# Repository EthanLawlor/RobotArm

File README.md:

# 🤖 Desktop Robot Arm

A compact, fully customizable desktop robot arm designed for small-scale automation tasks. Developed as part of a Bachelor of Engineering in Mechatronics at Technological University Dublin, this project integrates 3D-printed components, servo motor actuation, custom electronics, Arduino-based firmware, Bluetooth control, and an Android app interface.

*Figure: CAD render of the assembled Desktop Robot Arm*

---

## 📦 Features

- 6 Degrees of Freedom using MG66R and SG90 servo motors  
- Bluetooth-enabled control with HC-05 and MIT App Inventor  
- Android app with presets and direct manual controls  
- Custom PCB with schematics and Gerber files (KiCAD)  
- Modular 3D-printed design with STL files included  
- Smooth servo motion using filtering algorithms  

---

## 📁 Repository Structure

1. **Documentation**  
   - `RobotArm-ProjectReport.pdf` – Full project report with design, testing, and results

2. **Electrical**  
   - `KiCAD-PCB/` – Circuit schematics, custom PCB layout, and Gerber files

3. **Mechanical**  
   - `STL-Files/` – 3D-printable mechanical components  
   - Includes exploded views and CAD drawings

4. **Software**  
   - `Arduino-Firmware/` – Code for ATmega328P (Arduino)  
   - `MIT-App-Inventor/` – Android app `.aia` source and `.apk` installer

---

## 🔧 Hardware Overview

- **Microcontroller:** ATmega328P (Arduino Uno or custom board)  
- **Servos:** 5× MG66R, 1× SG90  
- **Peak Current Draw:** 2.8A (measured)  
- **Bluetooth Module:** HC-05  
- **Build Volume:** 135mm x 90mm footprint  
- **Chassis:** Fully 3D-printed components (PLA)  

---

## 📱 Android App

- Built with **MIT App Inventor**  
- Control individual servo angles or trigger gesture presets:
  - `Home`, `Ready`, `Wave`, `Screwdriver`, `Circles`, `Diagonals`, `Worm`, `Demo`
- Bluetooth communication with Arduino via HC-05  

---

## 📐 Mechanical Design

- All STL files for 3D printing included  
- Exploded views, BOM, and design drawings available  
- Desktop-sized and modular for easy assembly and customization  

---

## 🔌 Electrical Design

- Custom PCB designed in **KiCAD**  
- Includes:
  - Circuit schematics  
  - PCB layout  
  - Gerber files for fabrication  
- Power and signal headers for servos, Bluetooth, and logic  

---

## 🧠 Arduino Firmware Features

- Servo smoothing for fluid movement  
- Bluetooth and Serial input parsing  
- Support for:
  - Comma-delimited angle commands (e.g., `90,90,90,90,90,90*`)
  - Keyword triggers (`Demo`, `Home`, etc.)
  - Real-time smoothing level adjustment (`0#/100#`)  

---

## 🚀 Getting Started

### 🔩 Requirements

- Arduino IDE  
- Android device with Bluetooth  
- 3D printer (recommended material: PLA)  
- 5V power supply (min. 3A)  
- HC-05 Bluetooth module  
- Basic tools for assembly and soldering  

### 🛠️ Setup Instructions

1. **3D Print** all components from the `STL-Files/` folder.  
2. **Assemble** using provided CAD diagrams.  
3. **Upload firmware** from `Arduino-Firmware/` to your ATmega328P.  
4. **Install Android app** from `MIT-App-Inventor/` (`.apk`) or open `.aia` to modify.  
5. **Pair Bluetooth** module and connect via the app.  
6. **Power on** the system and start experimenting!  

---

## 📚 Documentation

📄 Full design details, diagrams, testing results, and methodology can be found in the [Project Report (PDF)](./0.Documentation/RobotArm-ProjectReport.pdf).

---

## 🧩 Future Improvements

- Add tactile or force sensors  
- Integrate IoT control (Wi-Fi, MQTT)  
- Implement gesture learning via AI  
- Design swappable gripper attachments  
- Develop an educational kit version  

---

## 📝 License

This project is open-source and distributed under the terms of the [GNU General Public License v3.0 (GPL-3.0)](./LICENSE).

---

## 👤 Author

**Ethan Lawlor**  
B.Eng. Mechatronics  
Technological University Dublin

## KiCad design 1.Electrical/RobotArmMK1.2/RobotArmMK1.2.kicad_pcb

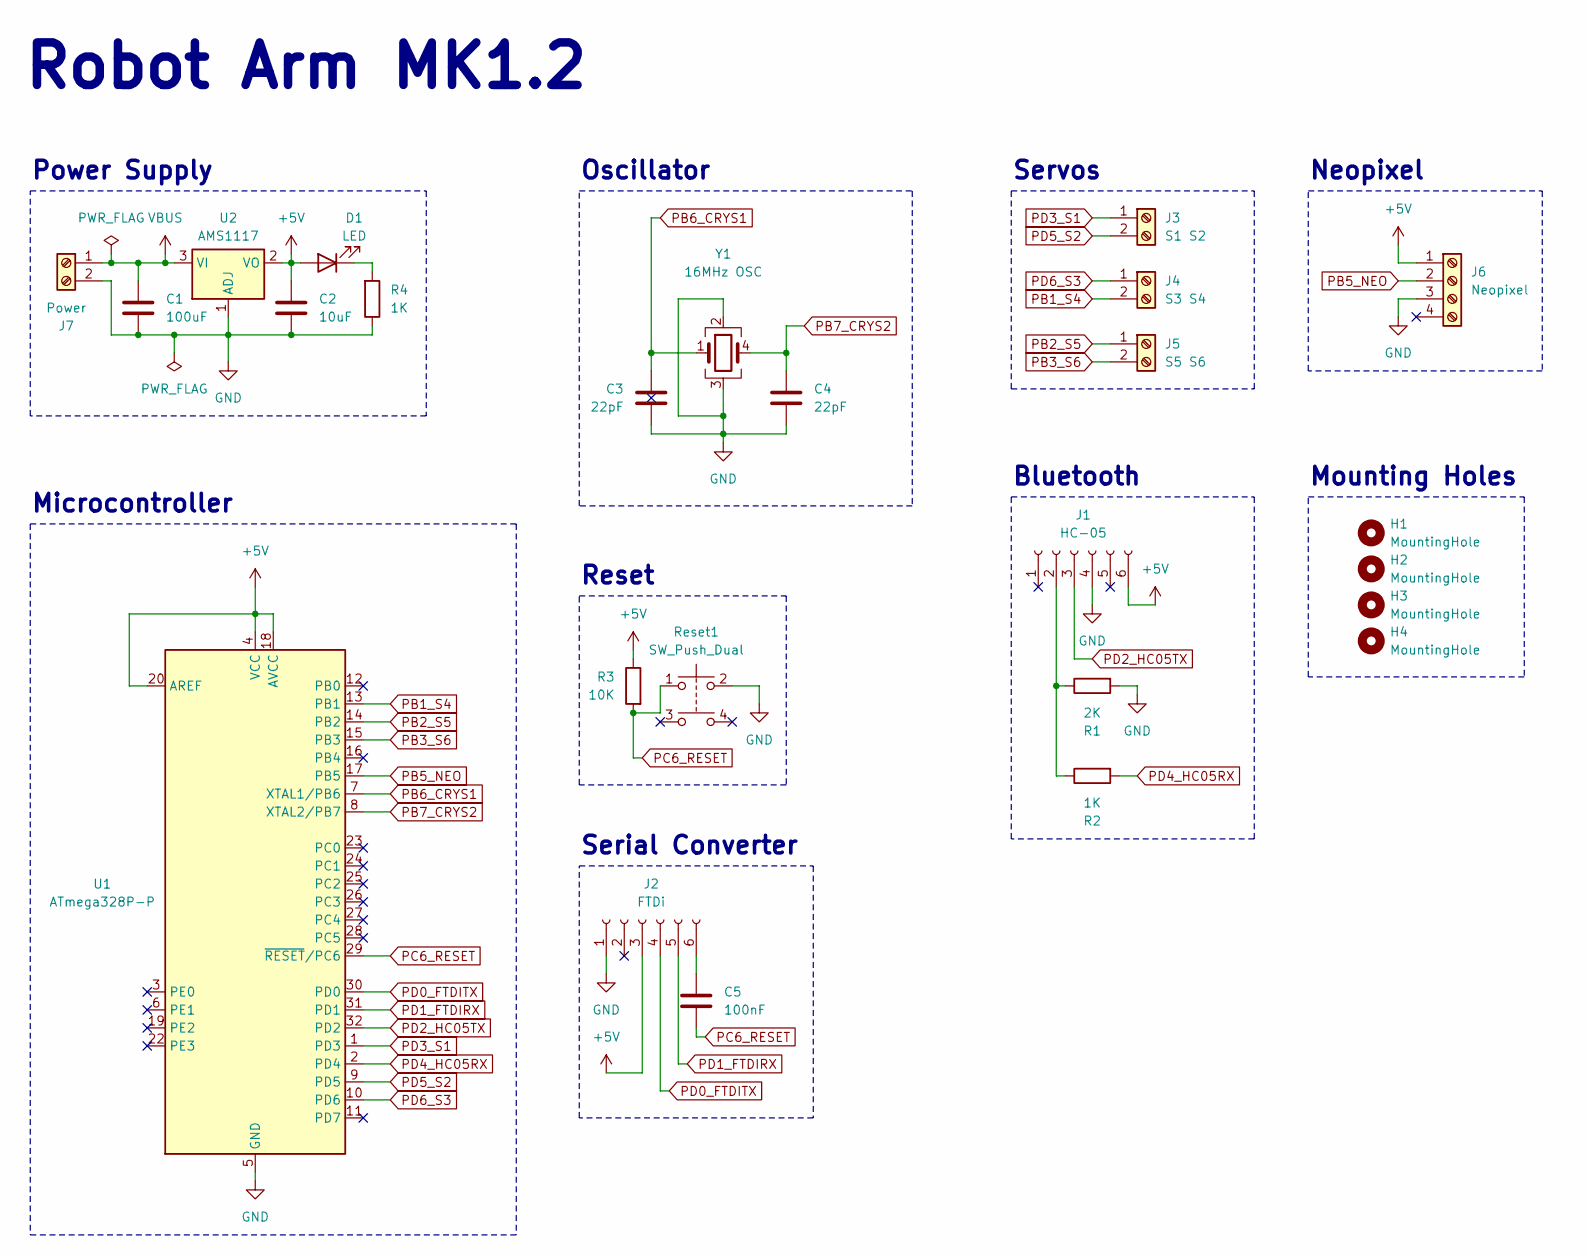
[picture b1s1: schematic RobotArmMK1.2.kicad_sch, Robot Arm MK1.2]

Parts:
C1: 100uF; TAJB_AVX-M
C2: 10uF; C_1206_3216Metric_Pad1.33x1.80mm_HandSolder
C3, C4: 22pF; C_0201_0603Metric_Pad0.64x0.40mm_HandSolder
C5: 100nF; C_0201_0603Metric_Pad0.64x0.40mm_HandSolder
D1: LED; LED_0603_1608Metric_Pad1.05x0.95mm_HandSolder
H1, H2, H3, H4: MountingHole; MountingHole_2.2mm_M2
J1: HC-05; TerminalBlock_TE_282834-6_1x06_P2.54mm_Horizontal
J2: FTDi; TerminalBlock_TE_282834-6_1x06_P2.54mm_Horizontal
J3: S1 S2; TerminalBlock_TE_282834-2_1x02_P2.54mm_Horizontal
J4: S3 S4; TerminalBlock_TE_282834-2_1x02_P2.54mm_Horizontal
J5: S5 S6; TerminalBlock_TE_282834-2_1x02_P2.54mm_Horizontal
J6: Neopixel; TerminalBlock_TE_282834-4_1x04_P2.54mm_Horizontal
J7: Power; TerminalBlock_TE_282834-2_1x02_P2.54mm_Horizontal
R1: 2K; R_0805_2012Metric_Pad1.20x1.40mm_HandSolder
R2, R4: 1K; R_0805_2012Metric_Pad1.20x1.40mm_HandSolder
R3: 10K; R_0805_2012Metric_Pad1.20x1.40mm_HandSolder
Reset1: SW_Push_Dual; SW_Push_1P1T_NO_6x6mm_H9.5mm
U1: ATmega328P-P; TQFP-32_7x7mm_P0.8mm
U2: AMS1117; TO-252-2
Y1: 16MHz OSC; Oscillator_SMD_ECS_2520MV-xxx-xx-4Pin_2.5x2.0mm

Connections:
+5V: C2.1, D1.2 (A), J1.6, J2.3, J6.1, R3.1, U1.4 (VCC), U1.18 (AVCC), U1.20 (AREF), U2.2 (VO)
GND: C1.2, C2.2, C3.2, C4.2, J1.4, J2.1, J6.3, J7.2, R1.2, R4.1, Reset1.2, U1.5 (GND), U1.21 (GND), U2.1 (ADJ), Y1.2, Y1.3
unnamed: D1.1 (K), R4.2
unnamed: J1.2, R1.1, R2.1
unnamed: C5.1, J2.6
PB1_S4: J4.2, U1.13 (PB1)
PB2_S5: J5.1, U1.14 (PB2)
PB3_S6: J5.2, U1.15 (PB3)
PB5_NEO: J6.2, U1.17 (PB5)
PB6_CRYS1: C3.1, U1.7 (XTAL1/PB6), Y1.1
PB7_CRYS2: C4.1, U1.8 (XTAL2/PB7), Y1.4
PC6_RESET: C5.2, R3.2, Reset1.1, U1.29 (~RESET/PC6)
PD0_FTDITX: J2.4, U1.30 (PD0)
PD1_FTDIRX: J2.5, U1.31 (PD1)
PD2_HC05TX: J1.3, U1.32 (PD2)
PD3_S1: J3.1, U1.1 (PD3)
PD4_HC05RX: R2.2, U1.2 (PD4)
PD5_S2: J3.2, U1.9 (PD5)
PD6_S3: J4.1, U1.10 (PD6)
VBUS: C1.1, J7.1, U2.3 (VI)

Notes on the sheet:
Power Supply
Serial Converter
Neopixel
Robot Arm MK1.2
Microcontroller
Servos
Oscillator
Reset
Mounting Holes
Bluetooth

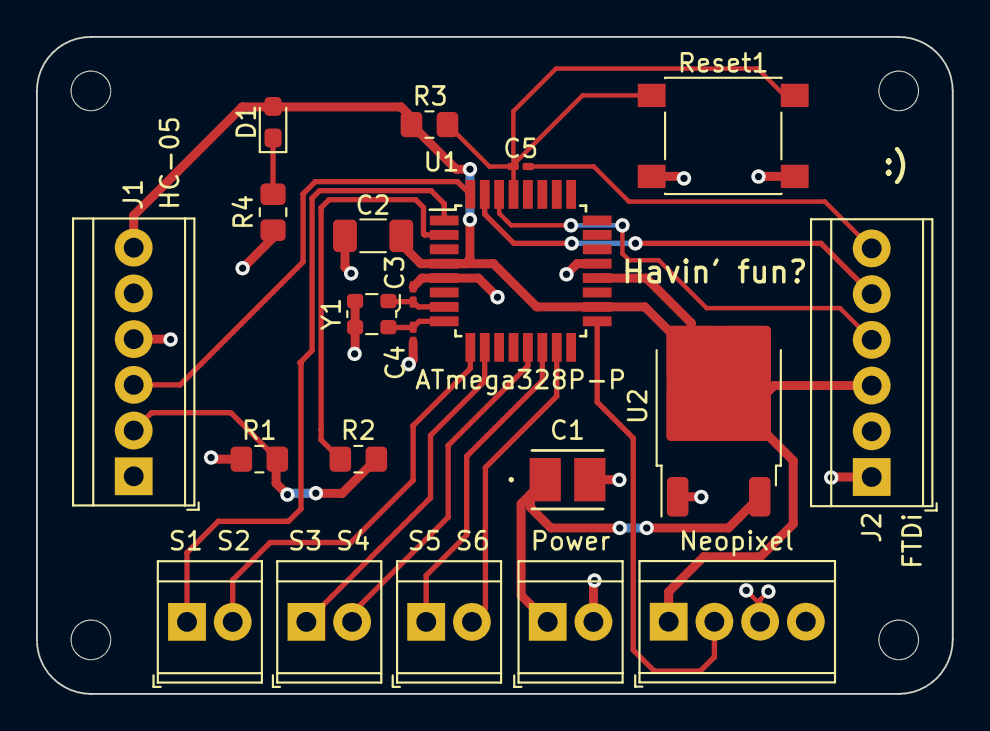
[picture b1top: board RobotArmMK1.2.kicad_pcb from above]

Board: 2 copper layers, 50.9 x 36.5 mm, 25 parts (0 on the bottom side), 20 nets.
